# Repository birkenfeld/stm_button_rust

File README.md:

## Make sound with STM32L0

### Build

Using nightly Rust and cargo, just do a `cargo build --release`.

### Flash

The default method uses openocd and GDB.  Start openocd using a config
matching your programming adapter (the provided `openocd.cfg` assumes
ST-Link v2).  Then `cargo run --release` runs GDB, flashes and runs the
image.  `openocd` should just keep running in the background.

An alternate way is to use the `st-flash` utility.  To use this from
`cargo run --release`, change the runner in `.cargo/config`.

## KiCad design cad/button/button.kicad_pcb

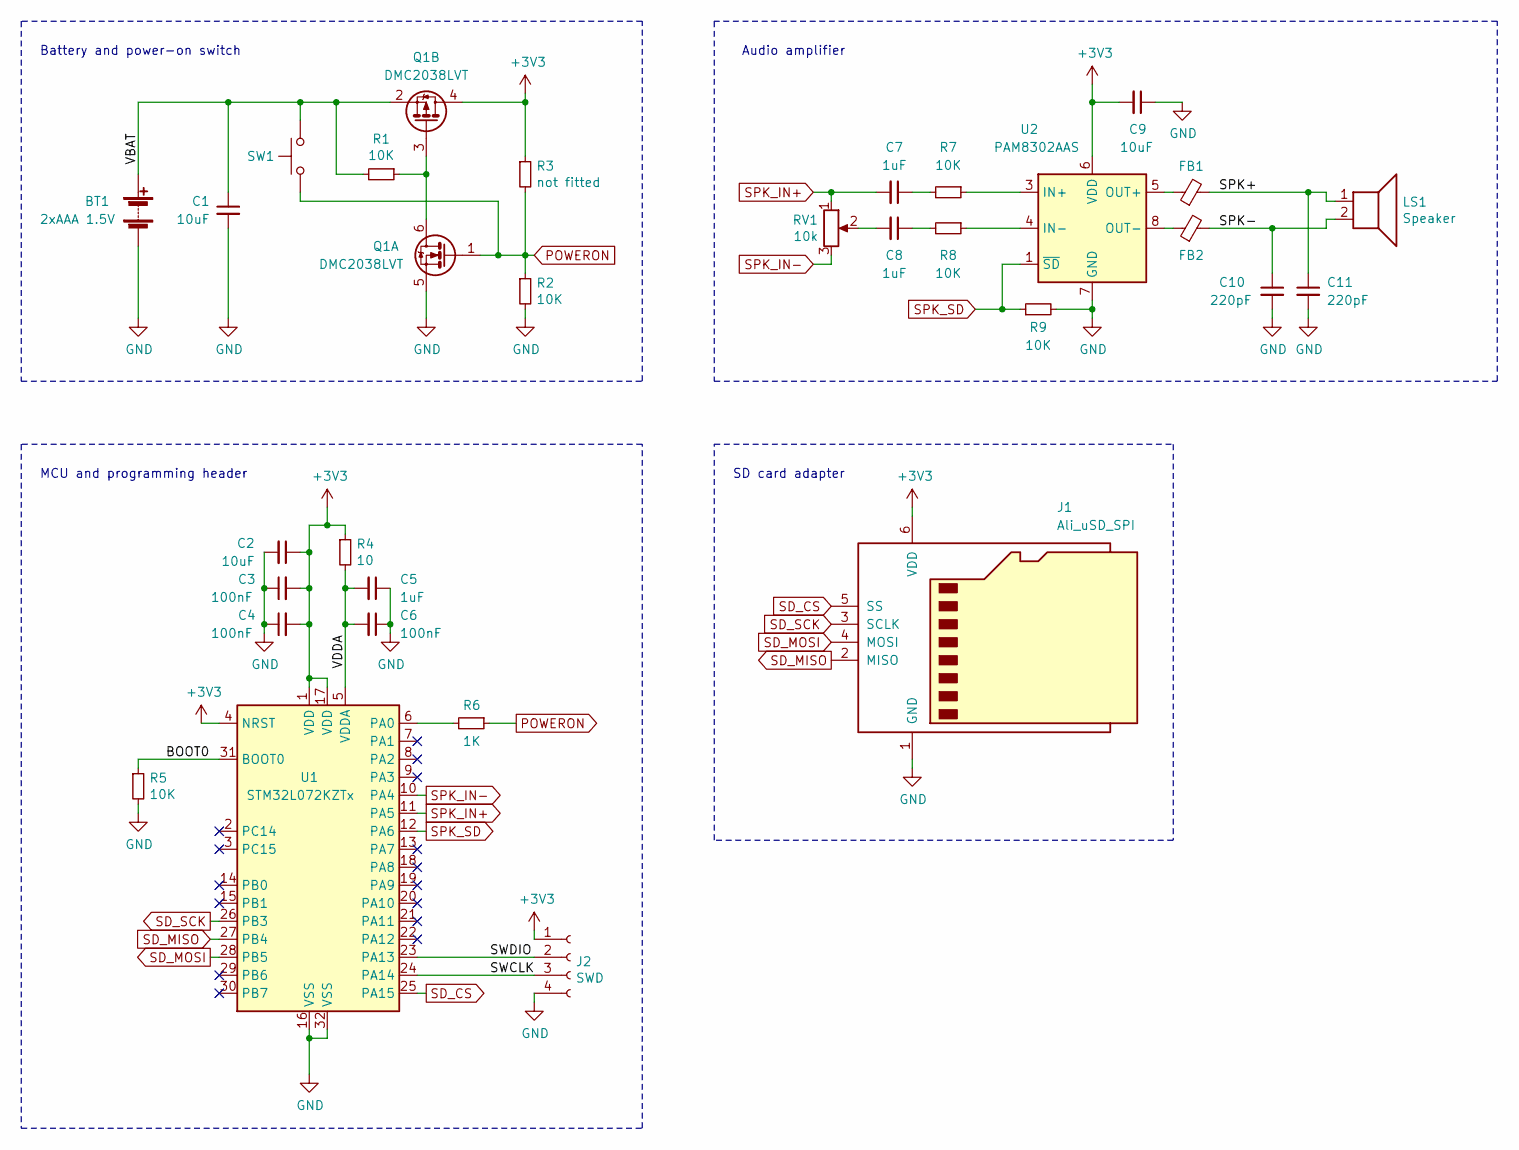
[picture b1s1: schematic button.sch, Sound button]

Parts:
BT1: 2xAAA 1.5V; Pad_2contacts
C1, C2, C9: 10uF; C_0603_1608Metric_Pad1.05x0.95mm_HandSolder
C3, C4, C6: 100nF; C_0603_1608Metric_Pad1.05x0.95mm_HandSolder
C5, C7, C8: 1uF; C_0603_1608Metric_Pad1.05x0.95mm_HandSolder
C10, C11: 220pF; C_0603_1608Metric_Pad1.05x0.95mm_HandSolder
FB1, FB2: Ferrite_Bead_Small; L_0603_1608Metric_Pad1.05x0.95mm_HandSolder
J1: Ali_uSD_SPI; Ali_uSD_Adapter
J2: SWD; Pad_4contacts
LS1: Speaker; Pad_2contacts
Q1: DMC2038LVT; TSOT-23-6_HandSoldering
R1, R2, R5, R7, R8, R9: 10K; R_0603_1608Metric_Pad1.05x0.95mm_HandSolder
R3: not fitted; R_0603_1608Metric_Pad1.05x0.95mm_HandSolder
R4: 10; R_0603_1608Metric_Pad1.05x0.95mm_HandSolder
R6: 1K; R_0603_1608Metric_Pad1.05x0.95mm_HandSolder
RV1: 10k; Potentiometer_Trimmer-EVM3Y
SW1: Button; SW_PUSH-12mm
U1: STM32L072KZTx; LQFP-32_7x7mm_P0.8mm
U2: PAM8302AAS; MSOP-8_3x3mm_P0.65mm

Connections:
+3V3: C2.1, C3.2, C4.2, C9.2, J1.6 (VDD), J2.1, Q1.4 (D), R3.1, R4.1, U1.1 (VDD), U1.4 (NRST), U1.17 (VDD), U2.6 (VDD)
/BOOT0: R5.1, U1.31 (BOOT0)
/SPK+: C11.1, FB1.2, LS1.1
/SPK-: C10.1, FB2.2, LS1.2
/SWCLK: J2.3, U1.24 (PA14)
/SWDIO: J2.2, U1.23 (PA13)
/VBAT: BT1.1 (+), C1.1, Q1.2 (S), R1.2, SW1.1
/VDDA: C5.2, C6.2, R4.2, U1.5 (VDDA)
GND: BT1.2 (-), C1.2, C2.2, C3.1, C4.1, C5.1, C6.1, C9.1, C10.2, C11.2, J1.1 (GND), J2.4, Q1.5 (S), R2.2, R5.2, R9.2, U1.16 (VSS), U1.32 (VSS), U2.7 (GND)
unnamed: C7.1, R7.2
unnamed: C8.1, R8.2
unnamed: C8.2, RV1.2
unnamed: FB1.1, U2.5 (OUT+)
unnamed: FB2.1, U2.8 (OUT-)
unnamed: Q1.3 (G), Q1.6 (D), R1.1
unnamed: R6.2, U1.6 (PA0)
unnamed: R7.1, U2.3 (IN+)
unnamed: R8.1, U2.4 (IN-)
POWERON: Q1.1 (G), R2.1, R3.2, R6.1, SW1.2
SD_CS: J1.5 (SS), U1.25 (PA15)
SD_MISO: J1.2 (MISO), U1.27 (PB4)
SD_MOSI: J1.4 (MOSI), U1.28 (PB5)
SD_SCK: J1.3 (SCLK), U1.26 (PB3)
SPK_IN+: C7.2, RV1.1, U1.11 (PA5)
SPK_IN-: RV1.3, U1.10 (PA4)
SPK_SD: R9.1, U1.12 (PA6), U2.1 (~SD)

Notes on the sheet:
Battery and power-on switch
MCU and programming header
Audio amplifier
SD card adapter

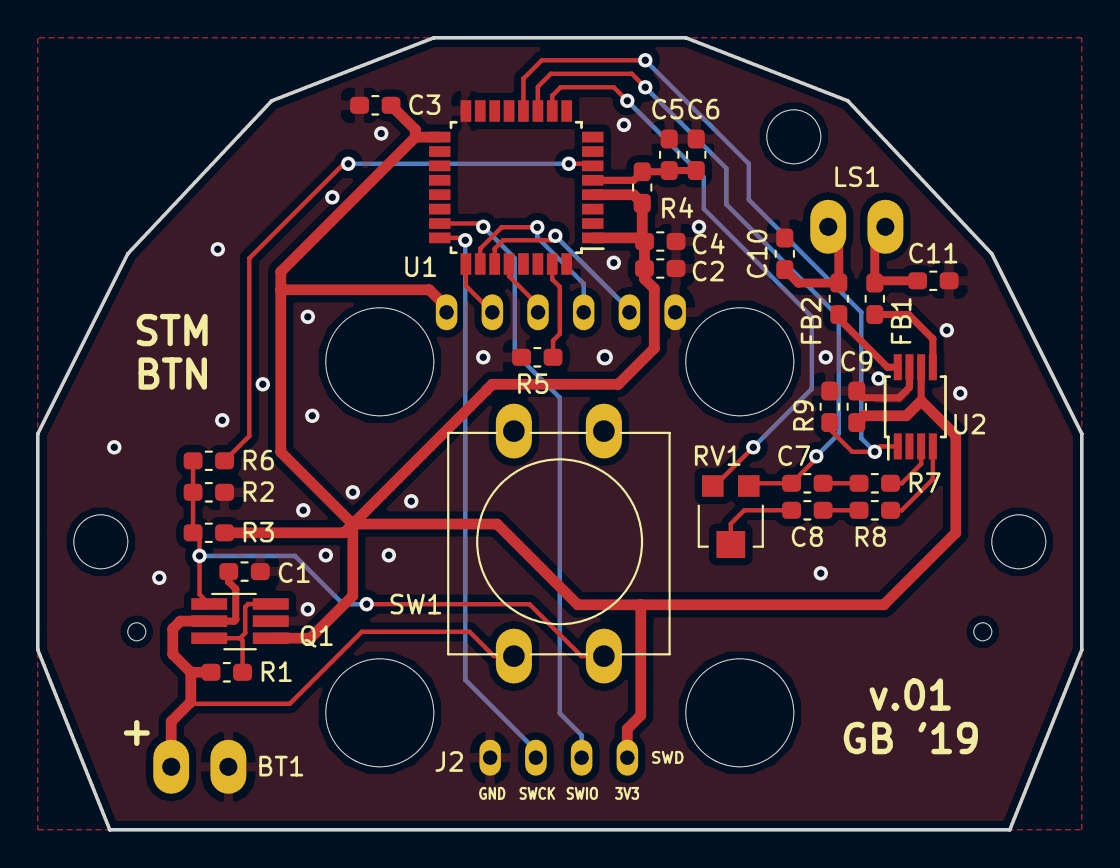
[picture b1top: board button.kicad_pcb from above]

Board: 2 copper layers, 58.0 x 44.0 mm, 31 parts (1 on the bottom side), 26 nets.

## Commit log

2018-12-19 initial commit, standby and wakeup working
2019-01-13 start on board drawing
2019-01-14 more drawing
2019-01-14 finish up schematic
2019-01-14 move STM to below sdcard
2019-01-15 update with help from Enno
2019-01-18 sdcard working
2019-01-18 dma audio from sdcard
2019-01-18 fixup DMA handling, audio now clear
2019-01-19 use sdmmc code from repo
2019-01-20 update Pot footprint
2019-01-20 prepare for other sdcard adapter
2019-01-21 move to kicad 5 footprints
2019-01-26 update sdmmc lib
2021-05-31 update dependencies
